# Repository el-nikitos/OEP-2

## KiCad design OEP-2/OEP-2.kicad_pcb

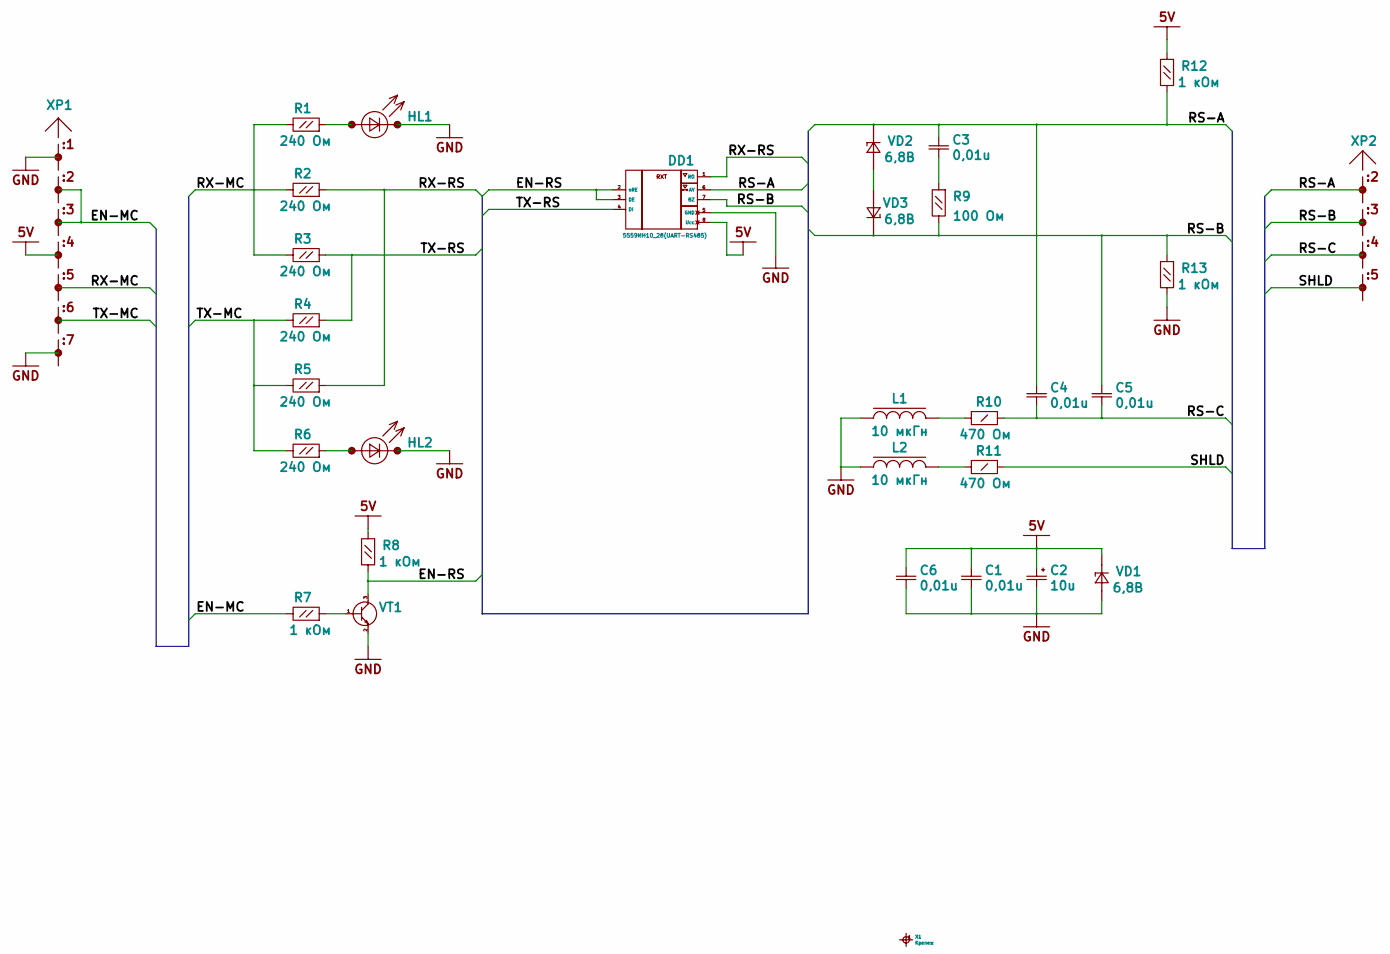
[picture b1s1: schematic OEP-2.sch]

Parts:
C1, C3, C4, C5, C6: Конденсатор_керамический; Конденсатор_SMD_IEC_0603
C2: Конденсатор_электролитический; CP_EIA-3528-21_Kemet-B_Pad1.50x2.35mm_HandSolder
DD1: 5559ИН10_28(UART-RS485); Микросхема_5559ИНхх
HL1, HL2: Светодиод; Светодиод_SMD_IEC_0603
L1, L2: Чип-индуктивность; Чип-индуктивность_SMD_0805
R1, R2, R3, R4, R5, R6, R7, R8, R9, R12, R13: Резистор_0,125Вт; Резистор_SMD_IEC_0805_0,125_Вт
R10, R11: Резистор_0,25Вт; Резистор_SMD_IEC_1206-0,25_Вт
VD1, VD2, VD3: Стабилитрон_КС168В2; Стабилитрон_корпус_КД-2_в_отверстие
VT1: Транзистор_2Т3130А9; Корпус_КТ-46
X1: Крепеж; Отверстие_М3
XP1: Вилка_СНП346-7ВП21-1#0; Вилка_СНП346-7ВП21-1-В
XP2: Вилка_СНП346-6ВП21-1#1N1N6; Вилка_СНП346-6ВП21-1-В

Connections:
5V: C1.1, C2.1, C6.1, DD1.8 (Ucc), R8.1, R12.1, VD1.K, XP1.4
/EN-MC: R7.2, XP1.2, XP1.3
/EN-RS: DD1.2 (nRE), DD1.3 (DE), R8.2, VT1.3
/RS-A: C3.1, C4.1, DD1.6 (AY), R12.2, VD2.K, XP2.2
/RS-B: C5.1, DD1.7 (BZ), R9.2, R13.1, VD3.K, XP2.3
/RS-C: C4.2, C5.2, R10.2, XP2.4
/RX-MC: R1.2, R2.2, R3.2, XP1.5
/RX-RS: DD1.1 (RO), R2.1, R5.1
/SHLD: R11.2, XP2.5
/TX-MC: R4.2, R5.2, R6.2, XP1.6
/TX-RS: DD1.4 (DI), R3.1, R4.1
GND: C1.2, C2.2, C6.2, DD1.5 (GND), HL1.K, HL2.K, L1.1, L2.1, R13.2, VD1.A, VT1.2, XP1.1, XP1.7
unnamed: C3.2, R9.1
unnamed: HL1.A, R1.1
unnamed: HL2.A, R6.1
unnamed: L1.2, R10.1
unnamed: L2.2, R11.1
unnamed: R7.1, VT1.1
unnamed: VD2.A, VD3.A

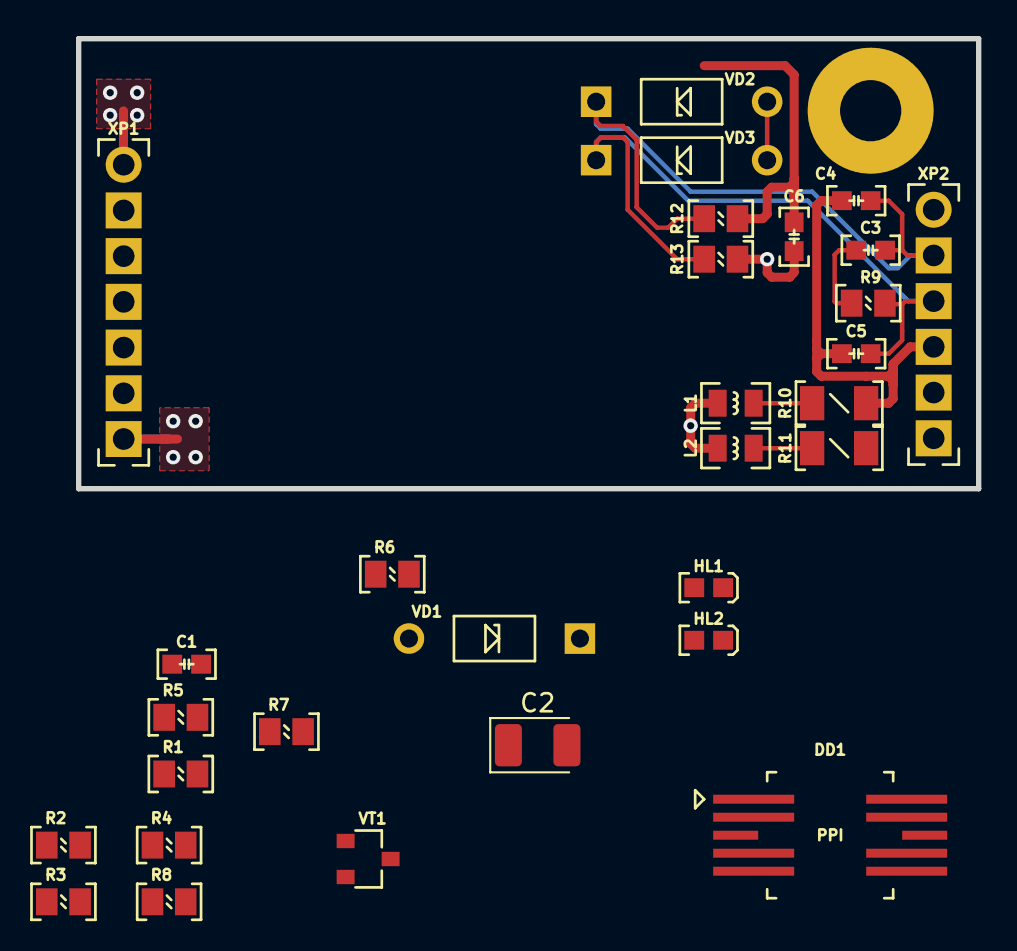
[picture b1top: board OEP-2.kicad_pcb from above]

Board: 2 copper layers, 50.0 x 25.0 mm, 31 parts (0 on the bottom side), 19 nets.

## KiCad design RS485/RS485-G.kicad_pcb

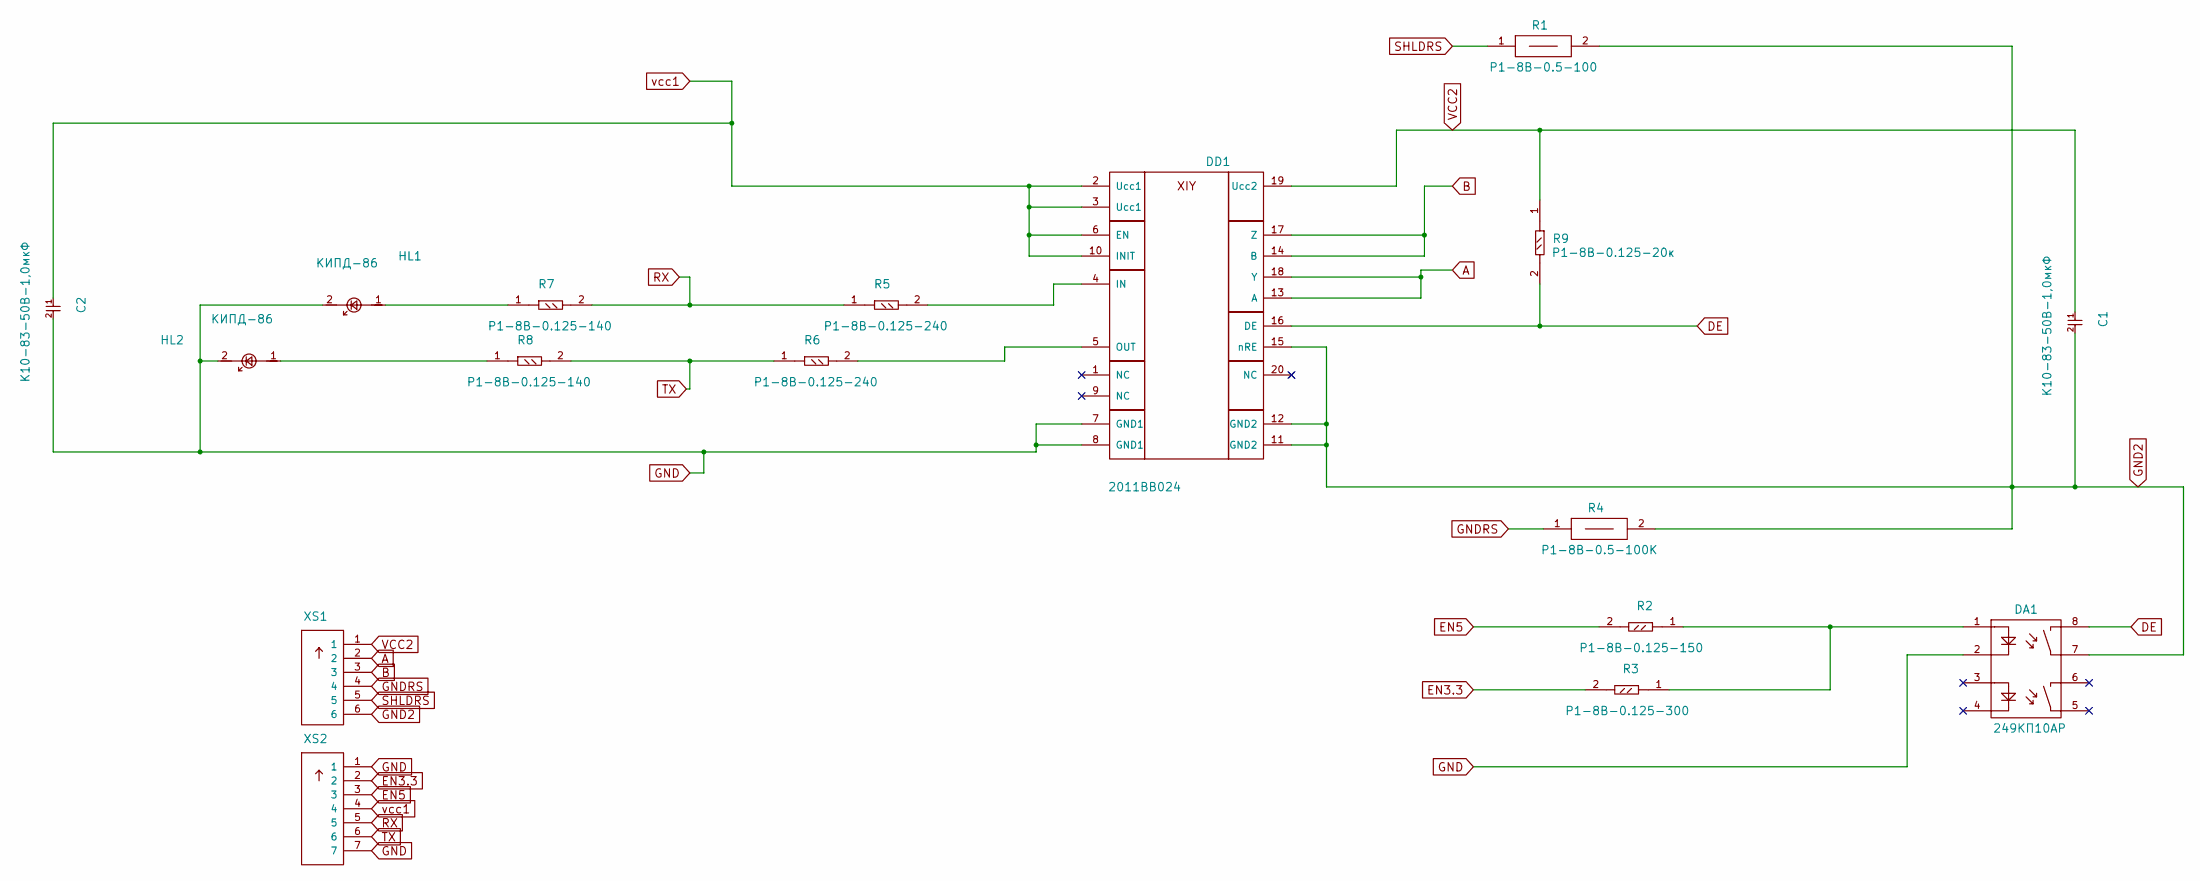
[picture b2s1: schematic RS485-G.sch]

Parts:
C1, C2: К10-83-50В-1,0мкФ; Конденсатор_SMD_1812
DA1: 249КП10AР; МОП-реле_249КП10(SMD)
DD1: 2011ВВ024
HL1, HL2: КИПД-86; Светодиод_SMD_3528
R1: Р1-8В-0.5-100; Резистор_SMD_2010-0,5_Вт
R2: Р1-8В-0.125-150; Резистор_SMD_0805_0,125Вт
R3: Р1-8В-0.125-300; Резистор_SMD_0805_0,125Вт
R4: Р1-8В-0.5-100К; Резистор_SMD_2010-0,5_Вт
R5, R6: Р1-8В-0.125-240; Резистор_SMD_0805_0,125Вт
R7, R8: Р1-8В-0.125-140; Резистор_SMD_0805_0,125Вт
R9: Р1-8В-0.125-20к; Резистор_SMD_0805_0,125Вт
XS1: Вилка_СНП346-6ВП21-1-В
XS2: Вилка_СНП346-7ВП21-1-В

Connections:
A: DD1.13 (A), DD1.18 (Y), XS1.2
B: DD1.14 (B), DD1.17 (Z), XS1.3
DE: DA1.8, DD1.16 (DE), R9.2
EN3.3: R3.2, XS2.2
EN5: R2.2, XS2.3
GND: C2.2, DA1.2, DD1.7 (GND1), DD1.8 (GND1), HL1.2, HL2.2, XS2.1, XS2.7
GND2: C1.2, DA1.7, DD1.11 (GND2), DD1.12 (GND2), DD1.15 (nRE), R1.2, R4.2, XS1.6
GNDRS: R4.1, XS1.4
unnamed: DA1.1, R2.1, R3.1
unnamed: DD1.4 (IN), R5.2
unnamed: DD1.5 (OUT), R6.2
unnamed: HL1.1, R7.1
unnamed: HL2.1, R8.1
RX: R5.1, R7.2, XS2.5
SHLDRS: R1.1, XS1.5
TX: R6.1, R8.2, XS2.6
VCC2: C1.1, DD1.19 (Ucc2), R9.1, XS1.1
vcc1: C2.1, DD1.2 (Ucc1), DD1.3 (Ucc1), DD1.6 (EN), DD1.10 (INIT), XS2.4

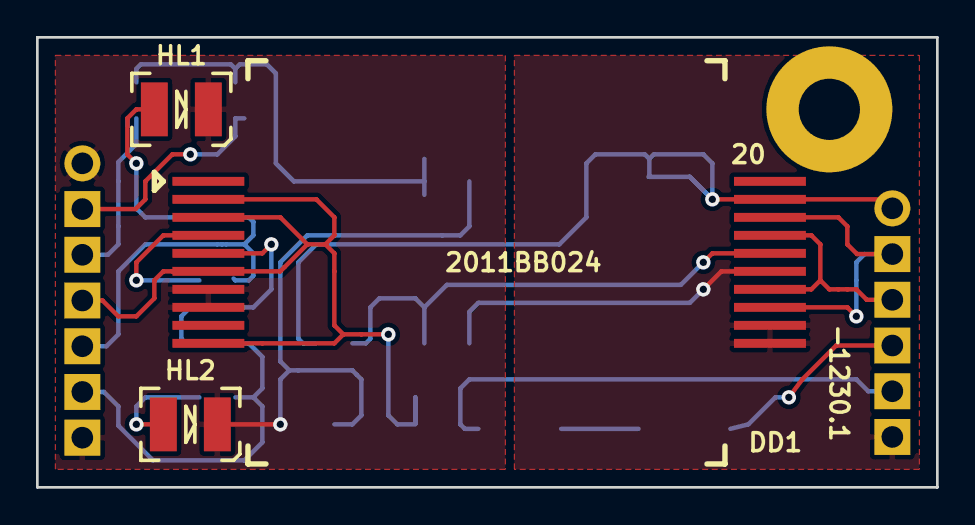
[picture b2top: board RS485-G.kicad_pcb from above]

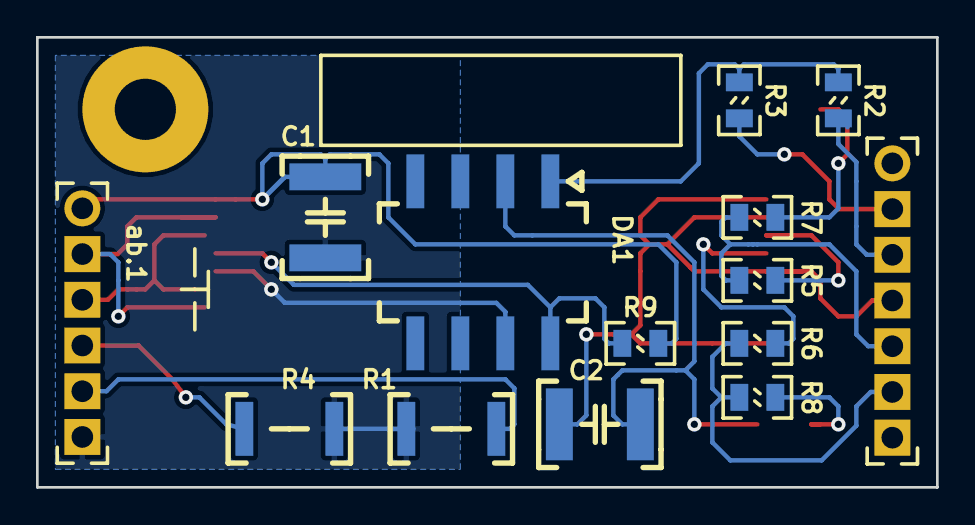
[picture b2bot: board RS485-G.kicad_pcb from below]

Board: 2 copper layers, 50.0 x 25.0 mm, 19 parts (15 on the bottom side), 18 nets.

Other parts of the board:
M3: ОтверстиеD3
Ref**: icon_motor_micro

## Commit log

2021-07-03 добавлен проект прототипа и начата схема
2021-07-03 подготовлена схема, определен габарит
2021-07-04 назначены посадочные места, кроме стабилитронов и тантала
2021-07-04 назначены все посадочные места, готов сегмент линий RS
2021-07-04 готова трассировка, подготовлены GBR
2021-07-04 обновлена схема в PDF
